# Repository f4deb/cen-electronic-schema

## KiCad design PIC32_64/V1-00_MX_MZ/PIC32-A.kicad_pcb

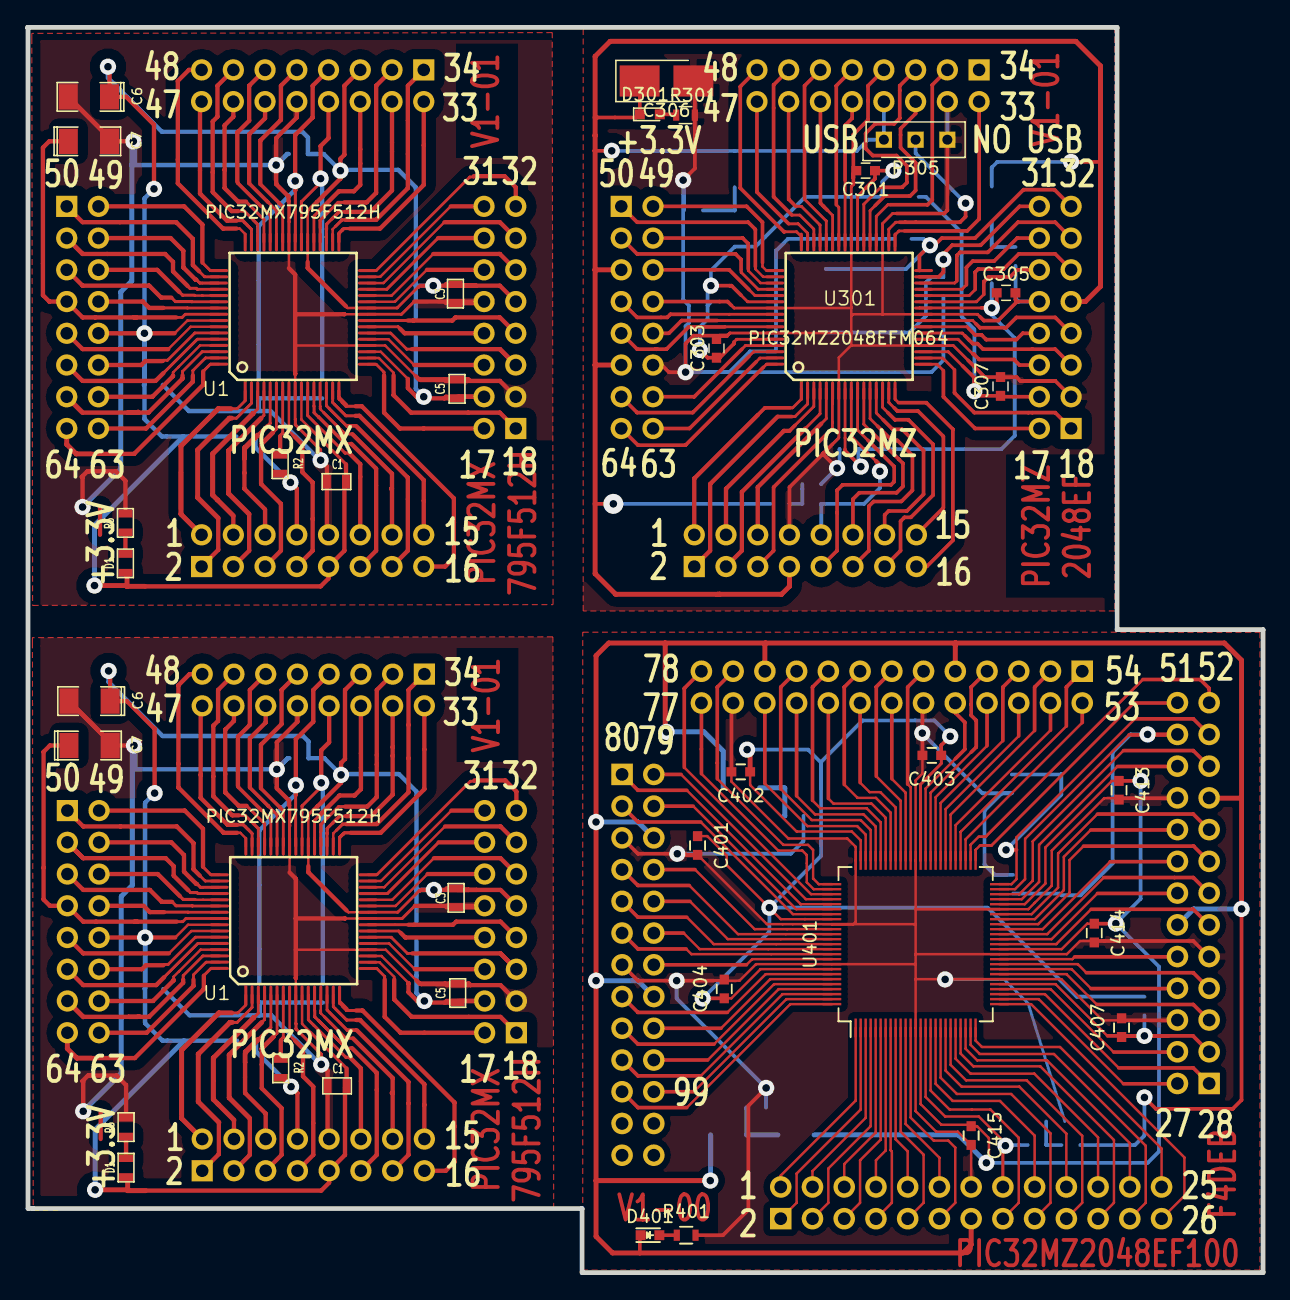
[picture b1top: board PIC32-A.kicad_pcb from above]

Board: 2 copper layers, 98.9 x 99.7 mm, 96 parts (0 on the bottom side), 213 nets.

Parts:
C1, C1#2, C2, C2#2, C3, C3#2, C4, C4#2, C5, C5#2, C8, C8#2, C9, C9#2: 100n; SM0603_Capa
C6, C6#2, C7, C7#2: 10u/10V; SM1206POL
C301, C302, C303, C304, C305, C307, C310, C401, C402, C403, C404, C407, C411, C413, C414, C415: 100n; C_0603
C306: 10u/10V; CP_Tantalum_Case-B_EIA-3528-21_Hand
C308, C309, C408, C409: 10n; C_0603
C311, C312, C410, C412: 22p; C_0603
D1, D1#2: LED; SM0603
D301, D401: LED; LED_0603
L301, L302, L303, L304, L401, L402, L403, L404: Ferrite_Bead_Small; R_1206
P1, P1#2, P2, P2#2, P3, P3#2, P4, P4#2, P301, P302, P303, P304: CONN_8X2; Socket_Strip_Straight_2x08_Pitch2.54mm
P305: CAVALIER2; SL-103-X-XX_1x03
P401, P402, P404, P405: CONN_13X2; Socket_Strip_Straight_2x13
R1, R1#2: 10k; SM0603_Resistor
R2, R2#2: 470; SM0603_Resistor
R3, R3#2: 1k; SM0603_Resistor
R4, R4#2: 0; SM0603_Resistor
R301, R303, R401, R403: 1k; R_0603
R302: 0; R_1206
R304, R404: 10k; R_0603
R402: 0; R_0603
U1, U1#2: PIC32MX795F512H; TQFP_64
U301: PIC32MZ2048EFM064; TQFP_64
U401: PIC32MZ2048EF100; TQFP-100_12x12mm_Pitch0.4mm
X1, X1#2: 8Mhz; QTZ
X301: 24Mhz; QTZ
X401: 24Mhz; Crystal_HC49-SD_SMD

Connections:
+3.3V: C1.1, C1#2.1, C2.1, C2#2.1, C3.1, C3#2.1, C4.1, C4#2.1, C6.1, C6#2.1, D1.1, D1#2.1, P1.9, P1#2.9, P2.5, P2#2.5, P3.9, P3#2.9, P4.10, P4#2.10, R1.2, R1#2.2, R4.1, R4#2.1, U1.10, U1.26, U1.38, U1.57, U1#2.10, U1#2.26, U1#2.38, U1#2.57
+3.3VA: D401.1, L401.1, L403.1, P401.13, P402.12, P402.19, P404.9, P404.21, P405.6, P405.16, R404.2
+3.3VP: C306.1, D301.1, L301.1, L303.1, P301.7, P302.9, P303.8, P304.5, P304.11, P305.1, R304.2
/1: P1.2, P1#2.2, U1.1, U1#2.1
/2: P1.1, P1#2.1, U1.2, U1#2.2
/3: P1.4, P1#2.4, U1.3, U1#2.3
/4: P1.3, P1#2.3, U1.4, U1#2.4
/5: P1.6, P1#2.6, U1.5, U1#2.5
/6: P1.5, P1#2.5, U1.6, U1#2.6
/7: P1.8, P1#2.8, R1.1, R1#2.1, R2.2, R2#2.2
/8: P1.7, P1#2.7, U1.8, U1#2.8
/11: P1.12, P1#2.12, U1.11, U1#2.11
/12: P1.11, P1#2.11, U1.12, U1#2.12
/13: P1.14, P1#2.14, U1.13, U1#2.13
/14: P1.13, P1#2.13, U1.14, U1#2.14
/15: P1.16, P1#2.16, U1.15, U1#2.15
/16: P1.15, P1#2.15, U1.16, U1#2.16
/17: P3.2, P3#2.2, U1.17, U1#2.17
/18: P3.1, P3#2.1, U1.18, U1#2.18
/19: C5.1, C5#2.1, P3.4, P3#2.4, R4.2, R4#2.2, U1.19, U1#2.19
/21: P3.6, P3#2.6, U1.21, U1#2.21
/22: P3.5, P3#2.5, U1.22, U1#2.22
/23: P3.8, P3#2.8, U1.23, U1#2.23
/24: P3.7, P3#2.7, U1.24, U1#2.24
/27: P3.12, P3#2.12, U1.27, U1#2.27
/28: P3.11, P3#2.11, U1.28, U1#2.28
/29: P3.14, P3#2.14, U1.29, U1#2.29
/30: P3.13, P3#2.13, U1.30, U1#2.30
/31: P3.16, P3#2.16, U1.31, U1#2.31
/32: P3.15, P3#2.15, U1.32, U1#2.32
/33: P2.2, P2#2.2, U1.33, U1#2.33
/34: P2.1, P2#2.1, U1.34, U1#2.34
/35: P2.4, P2#2.4, U1.35, U1#2.35
/36: P2.3, P2#2.3, U1.36, U1#2.36
/37: P2.6, P2#2.6, U1.37, U1#2.37
/39: C8.1, C8#2.1, P2.8, P2#2.8, U1.39, U1#2.39, X1.2, X1#2.2
/40: C9.1, C9#2.1, P2.7, P2#2.7, U1.40, U1#2.40, X1.1, X1#2.1
/42: P2.9, P2#2.9, U1.42, U1#2.42
/43: P2.12, P2#2.12, U1.43, U1#2.43
/44: P2.11, P2#2.11, U1.44, U1#2.44
/45: P2.14, P2#2.14, U1.45, U1#2.45
/46: P2.13, P2#2.13, U1.46, U1#2.46
/47: P2.16, P2#2.16, U1.47, U1#2.47
/48: P2.15, P2#2.15, U1.48, U1#2.48
/49: P4.2, P4#2.2, U1.49, U1#2.49
/50: P4.1, P4#2.1, U1.50, U1#2.50
/51: P4.4, P4#2.4, U1.51, U1#2.51
/52: P4.3, P4#2.3, U1.52, U1#2.52
/53: P4.6, P4#2.6, U1.53, U1#2.53
/54: P4.5, P4#2.5, U1.54, U1#2.54
/55: P4.8, P4#2.8, U1.55, U1#2.55
/56: C7.1, C7#2.1, P4.7, P4#2.7, U1.56, U1#2.56
/58: P4.9, P4#2.9, U1.58, U1#2.58
/59: P4.12, P4#2.12, U1.59, U1#2.59
/60: P4.11, P4#2.11, U1.60, U1#2.60
/61: P4.14, P4#2.14, U1.61, U1#2.61
/62: P4.13, P4#2.13, U1.62, U1#2.62
/63: P4.16, P4#2.16, U1.63, U1#2.63
/64: P4.15, P4#2.15, U1.64, U1#2.64
/PIC32MZ2048EF100/1: P401.2, U401.1
/PIC32MZ2048EF100/2: P401.1, U401.2
/PIC32MZ2048EF100/3: P401.4, U401.3
/PIC32MZ2048EF100/4: P401.3, U401.4
/PIC32MZ2048EF100/5: P401.6, U401.5
/PIC32MZ2048EF100/6: P401.5, U401.6
/PIC32MZ2048EF100/7: P401.8, U401.7
/PIC32MZ2048EF100/8: P401.7, U401.8
/PIC32MZ2048EF100/9: P401.10, U401.9
/PIC32MZ2048EF100/10: P401.9, U401.10
/PIC32MZ2048EF100/11: P401.12, U401.11
/PIC32MZ2048EF100/12: P401.11, U401.12
/PIC32MZ2048EF100/15: P401.16, R403.1, U401.15
/PIC32MZ2048EF100/16: P401.15, U401.16
/PIC32MZ2048EF100/17: P401.18, U401.17
/PIC32MZ2048EF100/18: P401.17, U401.18
/PIC32MZ2048EF100/19: P401.20, U401.19
/PIC32MZ2048EF100/20: P401.19, U401.20
/PIC32MZ2048EF100/21: P401.22, U401.21
/PIC32MZ2048EF100/22: P401.21, U401.22
/PIC32MZ2048EF100/23: P401.24, U401.23
/PIC32MZ2048EF100/24: P401.23, U401.24
/PIC32MZ2048EF100/25: P401.26, U401.25
/PIC32MZ2048EF100/26: P401.25, U401.26
/PIC32MZ2048EF100/27: P402.2, U401.27
/PIC32MZ2048EF100/28: P402.1, U401.28
/PIC32MZ2048EF100/29: P402.4, U401.29
/PIC32MZ2048EF100/30: C407.1, P402.3, R402.2, U401.30
/PIC32MZ2048EF100/32: P402.5, U401.32
/PIC32MZ2048EF100/33: P402.8, U401.33
/PIC32MZ2048EF100/34: P402.7, U401.34
/PIC32MZ2048EF100/35: P402.10, U401.35
/PIC32MZ2048EF100/38: P402.11, U401.38
/PIC32MZ2048EF100/39: P402.14, U401.39
/PIC32MZ2048EF100/40: P402.13, U401.40
/PIC32MZ2048EF100/41: P402.16, U401.41
/PIC32MZ2048EF100/42: P402.15, U401.42
/PIC32MZ2048EF100/43: P402.18, U401.43
/PIC32MZ2048EF100/44: P402.17, U401.44
/PIC32MZ2048EF100/47: P402.22, U401.47
/PIC32MZ2048EF100/48: P402.21, U401.48
/PIC32MZ2048EF100/49: C410.1, P402.24, U401.49, X401.2
/PIC32MZ2048EF100/50: C412.1, P402.23, U401.50, X401.1
/PIC32MZ2048EF100/51: P402.26, U401.51
/PIC32MZ2048EF100/52: P402.25, U401.52
/PIC32MZ2048EF100/53: P404.2, U401.53
/PIC32MZ2048EF100/54: P404.1, U401.54
/PIC32MZ2048EF100/55: P404.4, U401.55
/PIC32MZ2048EF100/56: P404.3, U401.56
/PIC32MZ2048EF100/57: P404.6, U401.57
/PIC32MZ2048EF100/58: P404.5, U401.58
/PIC32MZ2048EF100/59: P404.8, U401.59
/PIC32MZ2048EF100/60: P404.7, U401.60
/PIC32MZ2048EF100/61: P404.10, U401.61
/PIC32MZ2048EF100/64: P404.11, U401.64
/PIC32MZ2048EF100/65: P404.14, U401.65
/PIC32MZ2048EF100/66: P404.13, U401.66
/PIC32MZ2048EF100/67: P404.16, U401.67
/PIC32MZ2048EF100/68: P404.15, U401.68
/PIC32MZ2048EF100/69: P404.18, U401.69
/PIC32MZ2048EF100/70: P404.17, U401.70
/PIC32MZ2048EF100/71: P404.20, U401.71
/PIC32MZ2048EF100/72: P404.19, U401.72
/PIC32MZ2048EF100/73: P404.22, U401.73
/PIC32MZ2048EF100/76: P404.23, U401.76
/PIC32MZ2048EF100/77: P404.26, U401.77
/PIC32MZ2048EF100/78: P404.25, U401.78
/PIC32MZ2048EF100/79: P405.2, U401.79
/PIC32MZ2048EF100/80: P405.1, U401.80
/PIC32MZ2048EF100/81: P405.4, U401.81
/PIC32MZ2048EF100/82: P405.3, U401.82
/PIC32MZ2048EF100/85: P405.8, U401.85
/PIC32MZ2048EF100/86: P405.7, U401.86
/PIC32MZ2048EF100/87: P405.10, U401.87
/PIC32MZ2048EF100/88: P405.9, U401.88
/PIC32MZ2048EF100/89: P405.12, U401.89
/PIC32MZ2048EF100/90: P405.11, U401.90
/PIC32MZ2048EF100/91: P405.14, U401.91
/PIC32MZ2048EF100/94: P405.15, U401.94
/PIC32MZ2048EF100/95: P405.18, U401.95
/PIC32MZ2048EF100/96: P405.17, U401.96
/PIC32MZ2048EF100/97: P405.20, U401.97
/PIC32MZ2048EF100/98: P405.19, U401.98
/PIC32MZ2048EF100/99: P405.22, U401.99
/PIC32MZ2048EF100/100: P405.21, U401.100
/PIC32MZ20048EF64/1: P301.2, U301.1
/PIC32MZ20048EF64/2: P301.1, U301.2
/PIC32MZ20048EF64/3: P301.4, U301.3
/PIC32MZ20048EF64/4: P301.3, U301.4
/PIC32MZ20048EF64/5: P301.6, U301.5
/PIC32MZ20048EF64/6: P301.5, U301.6
/PIC32MZ20048EF64/9: P301.10, R303.1, U301.9
/PIC32MZ20048EF64/10: P301.9, U301.10
/PIC32MZ20048EF64/11: P301.12, U301.11
/PIC32MZ20048EF64/12: P301.11, U301.12
/PIC32MZ20048EF64/13: P301.14, U301.13
/PIC32MZ20048EF64/14: P301.13, U301.14
/PIC32MZ20048EF64/15: P301.16, U301.15
/PIC32MZ20048EF64/16: P301.15, U301.16
/PIC32MZ20048EF64/17: P302.2, U301.17
/PIC32MZ20048EF64/18: P302.1, U301.18
/PIC32MZ20048EF64/19: C307.1, P302.4, R302.2, U301.19
/PIC32MZ20048EF64/21: P302.6, U301.21
/PIC32MZ20048EF64/22: P302.5, U301.22
/PIC32MZ20048EF64/23: P302.8, U301.23
/PIC32MZ20048EF64/24: P302.7, U301.24
/PIC32MZ20048EF64/27: P302.12, U301.27
/PIC32MZ20048EF64/28: P302.11, U301.28
/PIC32MZ20048EF64/29: P302.14, U301.29
/PIC32MZ20048EF64/30: P302.13, U301.30
/PIC32MZ20048EF64/31: C312.1, P302.16, U301.31, X301.1
/PIC32MZ20048EF64/32: C311.1, P302.15, U301.32, X301.2
/PIC32MZ20048EF64/33: P303.2, U301.33
/PIC32MZ20048EF64/36: P303.3, U301.36
/PIC32MZ20048EF64/37: P303.6, U301.37
/PIC32MZ20048EF64/38: P303.5, U301.38
/PIC32MZ20048EF64/41: P303.10, U301.41
/PIC32MZ20048EF64/42: P303.9, U301.42
/PIC32MZ20048EF64/43: P303.12, U301.43
/PIC32MZ20048EF64/44: P303.11, U301.44
/PIC32MZ20048EF64/45: P303.14, U301.45
/PIC32MZ20048EF64/46: P303.13, U301.46
/PIC32MZ20048EF64/47: P303.16, U301.47
/PIC32MZ20048EF64/48: P303.15, U301.48
/PIC32MZ20048EF64/49: P304.2, U301.49
/PIC32MZ20048EF64/50: P304.1, U301.50
/PIC32MZ20048EF64/51: P304.4, U301.51
/PIC32MZ20048EF64/52: P304.3, U301.52
/PIC32MZ20048EF64/53: P304.6, U301.53
/PIC32MZ20048EF64/56: P304.7, U301.56
/PIC32MZ20048EF64/57: P304.10, U301.57
/PIC32MZ20048EF64/58: P304.9, U301.58
/PIC32MZ20048EF64/61: P304.14, U301.61
/PIC32MZ20048EF64/62: P304.13, U301.62
/PIC32MZ20048EF64/63: P304.16, U301.63
/PIC32MZ20048EF64/64: P304.15, U301.64
GND: C1.2, C1#2.2, C2.2, C2#2.2, C3.2, C3#2.2, C4.2, C4#2.2, C5.2, C5#2.2, C6.2, C6#2.2, C7.2, C7#2.2, C8.2, C8#2.2, C9.2, C9#2.2, P1.10, P1#2.10, P2.10, P2#2.10, P3.3, P3.10, P3#2.3, P3#2.10, R3.2, R3#2.2, U1.9, U1.20, U1.25, U1.41, U1#2.9, U1#2.20, U1#2.25, U1#2.41
GNDA: C401.2, C402.2, C403.2, C404.2, C407.2, C408.2, C409.2, C410.2, C411.2, C412.2, C413.2, C414.2, C415.2, P401.14, P402.6, P402.9, P402.20, P404.12, P404.24, P405.5, P405.13, R401.2, U401.13, U401.31, U401.36, U401.45, U401.63, U401.75, U401.84, U401.92
GNDD: C301.2, C302.2, C303.2, C304.2, C305.2, C306.2, C307.2, C308.2, C309.2, C310.2, C311.2, C312.2, P301.8, P302.3, P302.10, P303.4, P303.7, P304.8, P304.12, P305.3, R301.2, U301.7, U301.20, U301.25, U301.35, U301.40, U301.55, U301.59
unnamed: R2.1, R2#2.1, U1.7, U1#2.7
unnamed: D1.2, D1#2.2, R3.1, R3#2.1
unnamed: C301.1, C302.1, C303.1, L302.2, R302.1, U301.39, U301.54, U301.60
unnamed: C304.1, C305.1, L304.2, U301.8, U301.26
unnamed: C308.1, L301.2, L302.1
unnamed: C309.1, L303.2, L304.1
unnamed: C310.1, R303.2, R304.1
unnamed: C401.1, C402.1, C403.1, C404.1, L402.2, R402.1, U401.62, U401.74, U401.83, U401.93
unnamed: C408.1, L401.2, L402.1
unnamed: C409.1, L403.2, L404.1
unnamed: C411.1, R403.2, R404.1
unnamed: C413.1, C414.1, C415.1, L404.2, U401.14, U401.37, U401.46
unnamed: D301.2, R301.1
unnamed: D401.2, R401.1
unnamed: P305.2, U301.34

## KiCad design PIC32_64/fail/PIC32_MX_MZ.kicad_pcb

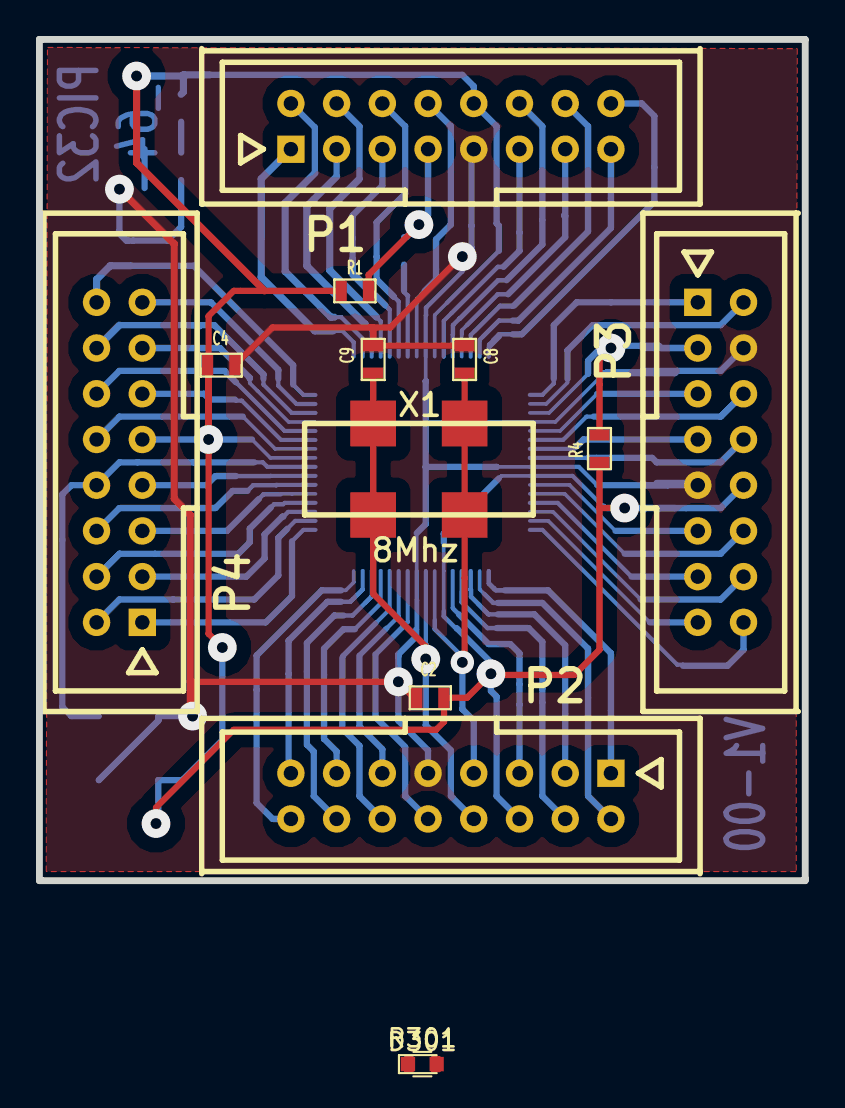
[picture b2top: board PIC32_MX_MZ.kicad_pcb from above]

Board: 2 copper layers, 42.5 x 46.7 mm, 22 parts (0 on the bottom side), 61 nets.

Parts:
C1, C2, C3, C4, C5: 100n; SM0603_Capa
C6, C7: 10u/10V; SM1206POL
C8, C9: 22p; SM0603_Capa
D1: LED; SM0603
D301: LED; LED_0603
P1, P2, P3, P4: CONN_8X2; he10-16d
R1: 10k; SM0603_Resistor
R2: 470; SM0603_Resistor
R3: 1k; SM0603_Resistor
R4: 0; SM0603_Resistor
R301: 1k; R_0603
U1: PIC32MX795F512H; TQFP_64
X1: 8Mhz; QTZ

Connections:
+3V3: C1.1, C2.1, C3.1, C4.1, C6.1, D1.1, P1.9, P2.5, P3.9, P4.10, R1.2, R4.1, U1.10, U1.26, U1.38, U1.57
/PIC32MX795F512H/1: P1.2, U1.1
/PIC32MX795F512H/2: P1.1, U1.2
/PIC32MX795F512H/3: P1.4, U1.3
/PIC32MX795F512H/4: P1.3, U1.4
/PIC32MX795F512H/5: P1.6, U1.5
/PIC32MX795F512H/6: P1.5, U1.6
/PIC32MX795F512H/7: P1.8, R1.1, R2.2
/PIC32MX795F512H/8: P1.7, U1.8
/PIC32MX795F512H/11: P1.12, U1.11
/PIC32MX795F512H/12: P1.11, U1.12
/PIC32MX795F512H/13: P1.14, U1.13
/PIC32MX795F512H/14: P1.13, U1.14
/PIC32MX795F512H/15: P1.16, U1.15
/PIC32MX795F512H/16: P1.15, U1.16
/PIC32MX795F512H/17: P3.2, U1.17
/PIC32MX795F512H/18: P3.1, U1.18
/PIC32MX795F512H/19: C5.1, P3.4, R4.2, U1.19
/PIC32MX795F512H/21: P3.6, U1.21
/PIC32MX795F512H/22: P3.5, U1.22
/PIC32MX795F512H/23: P3.8, U1.23
/PIC32MX795F512H/24: P3.7, U1.24
/PIC32MX795F512H/27: P3.12, U1.27
/PIC32MX795F512H/28: P3.11, U1.28
/PIC32MX795F512H/29: P3.14, U1.29
/PIC32MX795F512H/30: P3.13, U1.30
/PIC32MX795F512H/31: P3.16, U1.31
/PIC32MX795F512H/32: P3.15, U1.32
/PIC32MX795F512H/33: P2.2, U1.33
/PIC32MX795F512H/34: P2.1, U1.34
/PIC32MX795F512H/35: P2.4, U1.35
/PIC32MX795F512H/36: P2.3, U1.36
/PIC32MX795F512H/37: P2.6, U1.37
/PIC32MX795F512H/39: C8.1, P2.8, U1.39, X1.2
/PIC32MX795F512H/40: C9.1, P2.7, U1.40, X1.1
/PIC32MX795F512H/42: P2.9, U1.42
/PIC32MX795F512H/43: P2.12, U1.43
/PIC32MX795F512H/44: P2.11, U1.44
/PIC32MX795F512H/45: P2.14, U1.45
/PIC32MX795F512H/46: P2.13, U1.46
/PIC32MX795F512H/47: P2.16, U1.47
/PIC32MX795F512H/48: P2.15, U1.48
/PIC32MX795F512H/49: P4.2, U1.49
/PIC32MX795F512H/50: P4.1, U1.50
/PIC32MX795F512H/51: P4.4, U1.51
/PIC32MX795F512H/52: P4.3, U1.52
/PIC32MX795F512H/53: P4.6, U1.53
/PIC32MX795F512H/54: P4.5, U1.54
/PIC32MX795F512H/55: P4.8, U1.55
/PIC32MX795F512H/56: C7.1, P4.7, U1.56
/PIC32MX795F512H/58: P4.9, U1.58
/PIC32MX795F512H/59: P4.12, U1.59
/PIC32MX795F512H/60: P4.11, U1.60
/PIC32MX795F512H/61: P4.14, U1.61
/PIC32MX795F512H/62: P4.13, U1.62
/PIC32MX795F512H/63: P4.16, U1.63
/PIC32MX795F512H/64: P4.15, U1.64
GND: C1.2, C2.2, C3.2, C4.2, C5.2, C6.2, C7.2, C8.2, C9.2, P1.10, P2.10, P3.3, P3.10, R3.2, U1.9, U1.20, U1.25, U1.41
unnamed: D1.2, R3.1
unnamed: D301.2, R301.1
unnamed: R2.1, U1.7

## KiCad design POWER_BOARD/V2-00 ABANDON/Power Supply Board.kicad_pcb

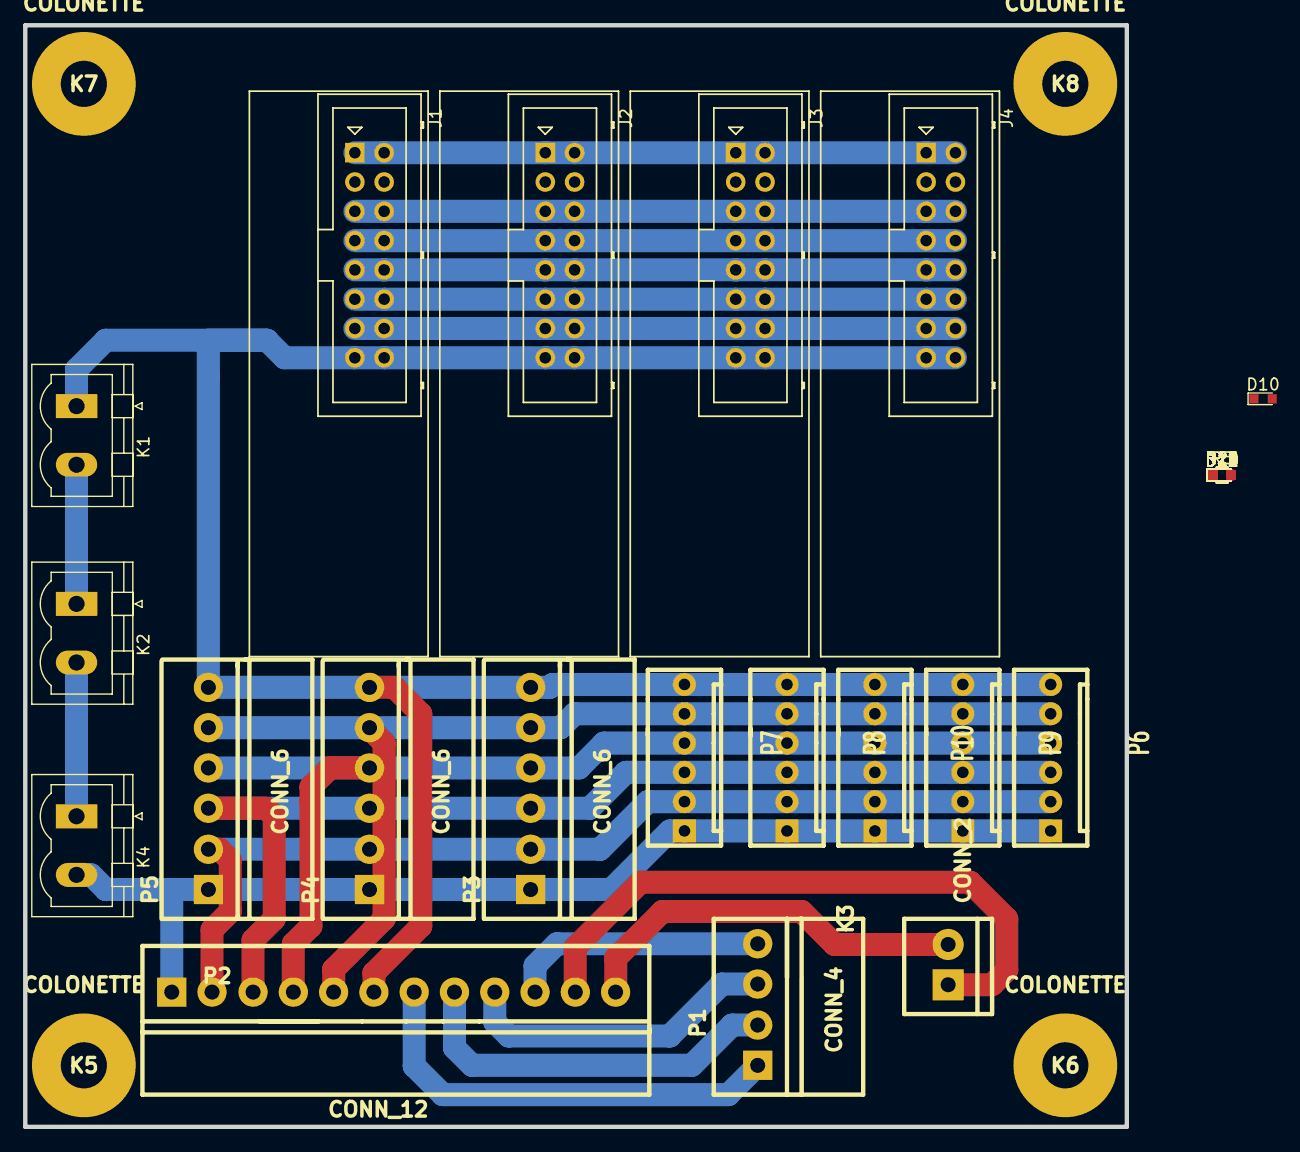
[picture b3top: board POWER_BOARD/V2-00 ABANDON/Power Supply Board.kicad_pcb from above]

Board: 2 copper layers, 95.5 x 95.5 mm, 32 parts (0 on the bottom side), 19 nets.

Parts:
D10, D11, D12, D13, D14: LED; LED_0603
J1, J2, J3, J4: CONN_02X08; POWER_BOARD_0-10
K1, K2, K4: CONN_2; PhoenixContact_MSTBVA-G_02x5.08mm_Vertical
K3: CONN_2; WEIDMULLER-2
K5, K6, K7, K8: COLONETTE
P1: CONN_4; WEIDMULLER-4
P2: CONN_12; WEIDMULLER-12
P3, P4, P5: CONN_6; WEIDMULLER-6
P6, P7, P8, P9, P10: CONN_6; KK-6
R5, R10: 3.3k; R_0603
R15, R20: 1k; R_0603
R21: 470; R_0603

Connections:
+3V3: D14.1, J1.13, J1.14, J2.13, J2.14, J3.13, J3.14, J4.13, J4.14, P2.5, P3.5, P4.5, P5.5, P6.5, P7.5, P8.5, P9.5, P10.5
+5V: D13.1, J1.11, J1.12, J2.11, J2.12, J3.11, J3.12, J4.11, J4.12, P2.4, P3.4, P4.4, P5.4, P6.4, P7.4, P8.4, P9.4, P10.4
+5VA: D12.1, J1.9, J1.10, J2.9, J2.10, J3.9, J3.10, J4.9, J4.10, P2.3, P3.3, P4.3, P5.3, P6.3, P7.3, P8.3, P9.3, P10.3
+12V: D11.1, J1.7, J1.8, J2.7, J2.8, J3.7, J3.8, J4.7, J4.8, P2.2, P3.2, P4.2, P5.2, P6.2, P7.2, P8.2, P9.2, P10.2
+BATT: D10.1, J1.5, J1.6, J2.5, J2.6, J3.5, J3.6, J4.5, J4.6, K4.2, P2.1, P3.1, P4.1, P5.1, P6.1, P7.1, P8.1, P9.1, P10.1
/M1A: P1.1, P2.7
/M1B: P1.2, P2.8
/M2A: P1.3, P2.9
/M2B: P1.4, P2.10
/M3A: K3.1, P2.11
/M3B: K3.2, P2.12
GND: J1.1, J1.2, J1.15, J1.16, J2.1, J2.2, J2.15, J2.16, J3.1, J3.2, J3.15, J3.16, J4.1, J4.2, J4.15, J4.16, K1.1, P2.6, P3.6, P4.6, P5.6, P6.6, P7.6, P8.6, P9.6, P10.6, R5.2, R10.2, R15.2, R20.2, R21.2
unnamed: D10.2, R5.1
unnamed: D11.2, R10.1
unnamed: D12.2, R15.1
unnamed: D13.2, R20.1
unnamed: D14.2, R21.1
unnamed: K1.2, K2.1
unnamed: K2.2, K4.1

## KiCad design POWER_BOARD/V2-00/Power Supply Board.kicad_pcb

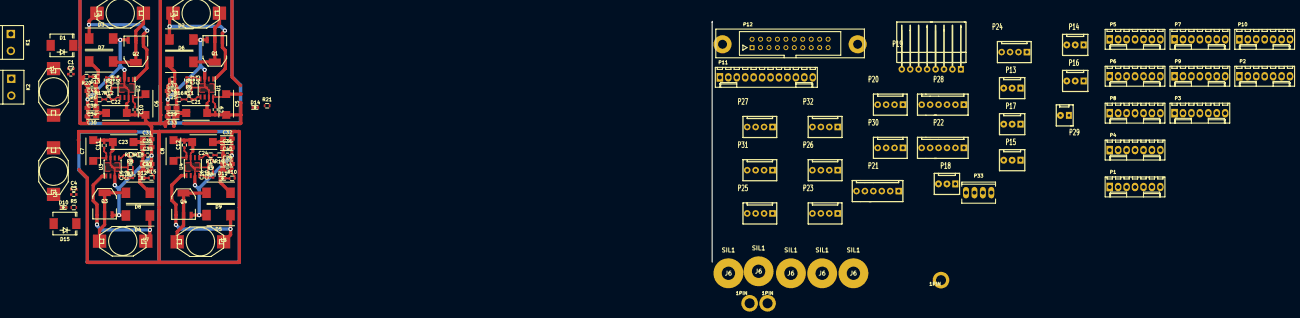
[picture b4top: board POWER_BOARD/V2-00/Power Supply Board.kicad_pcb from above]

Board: 2 copper layers, 137 parts (0 on the bottom side), 67 nets.

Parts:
1PIN, 1PIN#2, 1PIN#3: P***; 1pin
C1, C2, C3, C4, C9, C10, C11, C12: 47n; C_0603
C5, C6: 10µ/35V; TantalC_SizeD_EIA-7343_Reflow
C7, C8: 10µ/25V; TantalC_SizeD_EIA-7343_Reflow
C13, C14, C15, C16: 220p; C_0603
C17, C18, C19, C20: 22n; C_0603
C21, C22, C23, C24: CP; TantalC_SizeD_EIA-7343_Reflow
C25, C26, C27, C28, C29, C30, C31, C32, C33, C34, C35, C36: 100µ; TantalC_SizeA_EIA-3216_Reflow
C37, C38, C39, C40, C41, C42, C43, C44: 100n; C_0603
D1, D15: SMAJ36A; SMC_Standard
D2, D3, D4, D5, D6, D7, D8, D9: MBRS130LT3G; DO-214AB
D10, D11, D12, D13, D14: LED; LED_0603
J6, J6#2, J6#3, J6#4, J6#5: SIL1; COLONETTE
K1, K2: CONN_2; bornier2
L1, L3: 10µH/4.7A; Self_30_BiTech
L5, L6, L7, L8: 22µH/3.3A; Self_30_BiTech
P1, P2, P3, P4, P5, P6, P7, P8, P9, P10: CONN_7; Molex_KK-6410-07_07x2.54mm_Straight
P11: CONN_01X12; Molex_KK-6410-12_12x2.54mm_Straight
P12: CONN_02X20; HE10_20D
P13, P14, P15, P16, P17, P18: CONN_01X03; KK-3
P19: CONN_01X08; KK-8-H
P20: CONN_01X08; KK-4
P21: CONN_01X04; KK-6
P22, P28: CONN_01X06; KK-6
P23, P24, P25, P26, P27, P30, P31, P32: CONN_01X04; KK-4
P29: CONN_01X02; KK-2
P33: CONN_01X04; Socket_MOLEX-KK-RM2-54mm_Lock_4pin_straight
Q1, Q2, Q3: IRLL3303; SOT-223
Q4: Q_NMOS_GDSD; SOT-223
R1, R2, R3, R4: 4k7; R_0603
R5, R10: 3.3k; R_0603
R6, R7, R8: 3k3; R_0603
R9: 2k7; R_0603
R11: 5k6; R_0603
R12, R13: 10k; R_0603
R14: 22k; R_0603
R15, R17, R18, R20: 1k; R_0603
R16: 0; R_0603
R19: 2.2k; R_0603
R21: 470; R_0603
U1, U2, U3, U4: L5973D; SOIC-8_3.9x4.9mm_Pitch1.27mm

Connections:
+3V3: C21.1, C25.1, C29.1, C33.1, C37.1, C41.1, D6.1, D14.1, P1.2, P2.2, P3.2, P4.2, P5.2, P6.2, P7.2, P8.2, P9.2, P10.2, P11.5, R16.1
+5V: P11.3, P13.2, P14.2, P15.2, P16.2, P17.2, P18.2
+5VA: C23.1, C27.1, C31.1, C35.1, C39.1, C43.1, D8.1, D12.1, P1.4, P2.4, P3.4, P4.4, P5.4, P6.4, P7.4, P8.4, P9.4, P10.4, R18.1
+5VD: C22.1, C26.1, C30.1, C34.1, C38.1, C42.1, D7.1, D13.1, P1.5, P2.5, P3.5, P4.5, P5.5, P6.5, P7.5, P8.5, P9.5, P10.5, P11.4, P24.2, P25.2, P26.2, P27.3, P30.2, P31.2, P32.2, P33.2, R17.1
+5VP: C1.1, C2.1, D1.2, L1.1
+12P: C3.1, C4.1, D15.2, L3.1
+12V: P1.6, P2.6, P3.6, P4.6, P5.6, P6.6, P7.6, P8.6, P9.6, P10.6, P11.2
+12VA: C24.1, C28.1, C32.1, C36.1, C40.1, C44.1, D9.1, D11.1, R19.1
+15V: P11.1, P19.1, P28.6
+BATT: D10.1, K2.2, P1.7, P2.7, P3.7, P4.7, P5.7, P6.7, P7.7, P8.7, P9.7, P10.7
-5VA: P1.3, P2.3, P3.3, P4.3, P5.3, P6.3, P7.3, P8.3, P9.3, P10.3
/Connection/IO0: P12.9, P20.1
/Connection/IO1: P12.10, P20.2
/Connection/IO2: P12.11, P20.3
/Connection/IO3: P12.12, P20.4
/Connection/IRQ0: P12.17, P21.2
/Connection/IRQ1: P12.18, P21.3
/Connection/IRQ2: P12.20, P21.4
/Connection/M1A: P11.7, P28.2
/Connection/M1B: P11.8, P28.3
/Connection/M2A: P11.9, P28.4
/Connection/M2B: P11.10, P28.5
/Connection/M3A: P11.11, P29.1
/Connection/M3B: P11.12, P29.2
/Connection/RX: P12.5, P27.4
/Connection/SCL: P12.4, P24.3, P25.3, P26.3, P30.3, P31.3, P32.3, P33.3
/Connection/SDA: P12.3, P24.4, P25.4, P26.4, P30.4, P31.4, P32.4, P33.4
/Connection/SERV1: P13.3, P22.1
/Connection/SERV2: P14.3, P22.2
/Connection/SERV3: P15.3, P22.3
/Connection/SERV4: P16.3, P22.4
/Connection/SERV5: P17.3, P22.5
/Connection/SERV6: P18.3, P22.6
/Connection/TX: P12.6, P27.2
GND: C1.2, C2.2, C3.2, C4.2, C5.2, C6.2, C7.2, C8.2, C9.2, C10.2, C11.2, C12.2, C13.2, C14.2, C15.2, C16.2, C21.2, C22.2, C23.2, C24.2, C25.2, C26.2, C27.2, C28.2, C29.2, C30.2, C31.2, C32.2, C33.2, C34.2, C35.2, C36.2, C37.2, C38.2, C39.2, C40.2, C41.2, C42.2, C43.2, C44.2, D1.1, D2.2, D3.2, D4.2, D5.2, D15.1, K1.1, P1.1, P2.1, P3.1, P4.1, P5.1, P6.1, P7.1, P8.1, P9.1, P10.1, P11.6, P12.1, P12.2, P12.19, P13.1, P14.1, P15.1, P16.1, P17.1, P18.1, P19.2, P24.1, P25.1, P26.1, P27.1, P28.1, P30.1, P31.1, P32.1, P33.1, Q1.3, Q2.3, Q3.3, Q4.3, R1.2, R2.2, R3.2, R4.2, R5.2, R6.2, R7.2, R8.2, R9.2, R10.2, R15.2, R20.2, R21.2, U1.3, U1.7, U2.3, U2.7, U3.3, U3.7, U4.3, U4.7
unnamed: C5.1, C6.1, C9.1, C10.1, L1.2, U1.8, U2.8
unnamed: C7.1, C8.1, C11.1, C12.1, L3.2, U3.8, U4.8
unnamed: C13.1, C17.1, U1.4
unnamed: C14.1, C18.1, U2.4
unnamed: C15.1, C19.1, U3.4
unnamed: C16.1, C20.1, U4.4
unnamed: C17.2, R1.1
unnamed: C18.2, R2.1
unnamed: C19.2, R3.1
unnamed: C20.2, R4.1
unnamed: D2.1, L5.1, Q1.1, U1.1
unnamed: D3.1, L6.1, Q2.1, U2.1
unnamed: D4.1, L7.1, Q3.1, U3.1
unnamed: D5.1, L8.1, Q4.1, U4.1
unnamed: D6.2, L5.2, Q1.2
unnamed: D7.2, L6.2, Q2.2
unnamed: D8.2, L7.2, Q3.2
unnamed: D9.2, L8.2, Q4.2, Q4.4
unnamed: D10.2, R5.1
unnamed: D11.2, R10.1
unnamed: D12.2, R15.1
unnamed: D13.2, R20.1
unnamed: D14.2, R21.1
unnamed: K1.2, K2.1
unnamed: R11.1, R16.2
unnamed: R6.1, R11.2, U1.5
unnamed: R12.1, R17.2
unnamed: R7.1, R12.2, U2.5
unnamed: R13.1, R18.2
unnamed: R8.1, R13.2, U3.5
unnamed: R14.1, R19.2
unnamed: R9.1, R14.2, U4.5
